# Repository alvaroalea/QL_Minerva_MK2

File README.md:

# SINCLAIR QL - Minerva MK II - New OS + RTC

In 2024 by Alvaro Alea Fernandez

License under: CERN Open Hardware Licence Version 2 - Strongly Reciprocal

https://ohwr.org/cern_ohl_s_v2.txt

My work is only copy the design to Kicad, all (C) are retaing to the original owners.

U1 shall be pin row, to be mounted in the solder side, in a way that allow to insert on the Sinclair QL's Rom socket.

U5 shall be solder without socket under U2.

U2 shall be solder with a socket to allow space for U5.

Original Information of minerva can be found here: http://tfs.firshman.co.uk/ql/minerva.htm

A generic description here: https://wiki.qlforum.co.uk/doku.php?id=qlwiki:minerva

Manuals and software here: https://dilwyn.qlforum.co.uk/docs/manuals/index.html

Main information, GAL code, pictures, etc... has been obtained from this post: https://qlforum.co.uk/viewtopic.php?t=1993

ROM Chip shall be installed as per this picture:

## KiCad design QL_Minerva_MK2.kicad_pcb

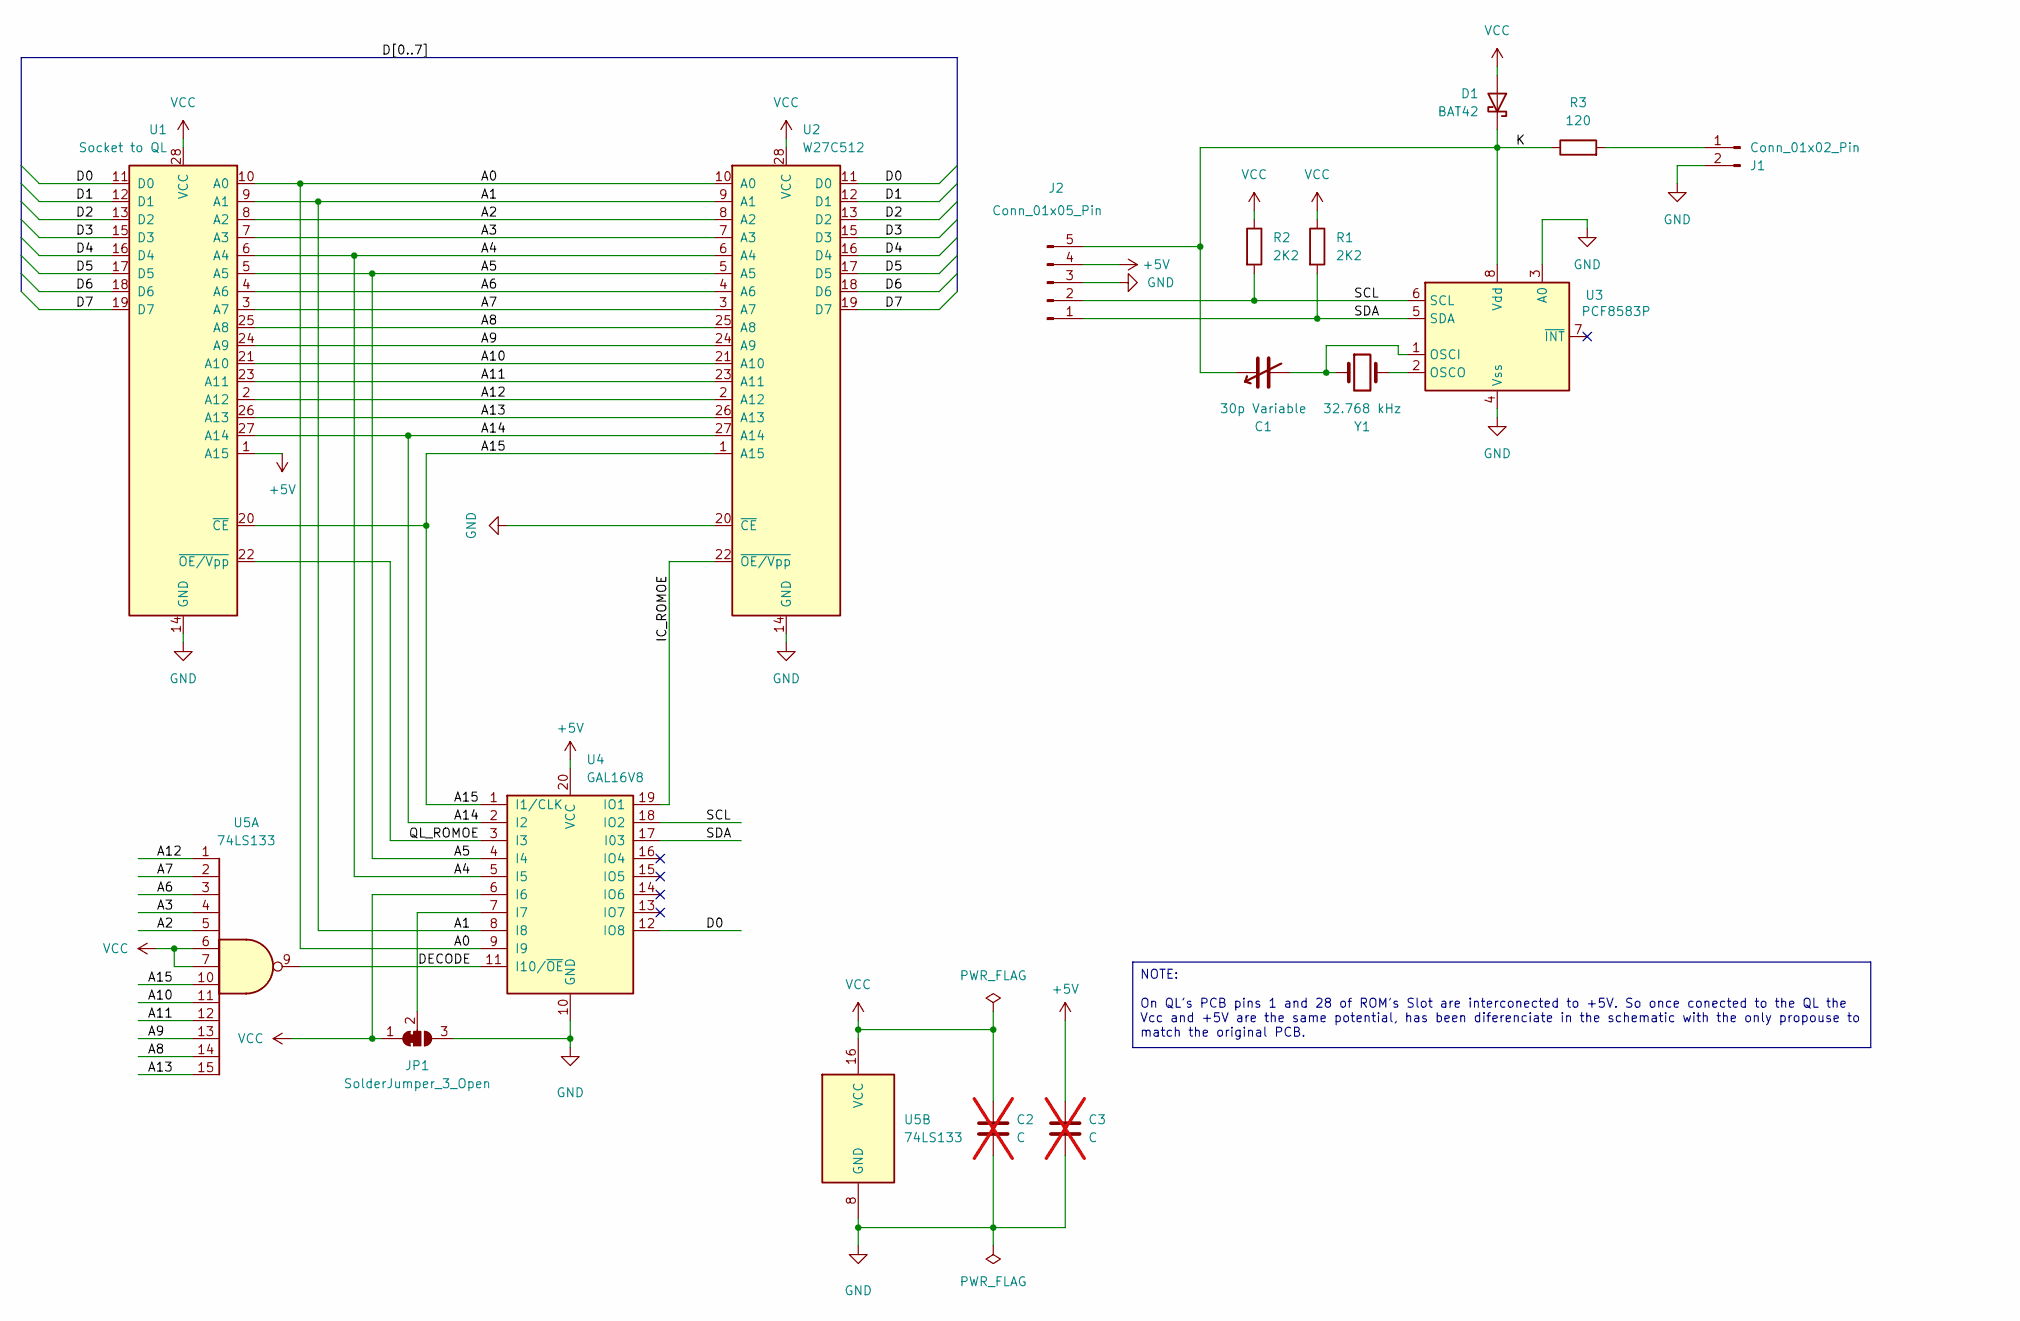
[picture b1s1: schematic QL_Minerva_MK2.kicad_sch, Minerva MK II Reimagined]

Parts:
C1: 30p Variable; C_Variable_Radial_D6.0mm_P5.00mm
C2, C3: C; C_Disc_D3.0mm_W1.6mm_P2.50mm; not fitted
D1: BAT42; D_DO-35_SOD27_P7.62mm_Horizontal
J1: Conn_01x02_Pin; PinHeader_1x02_P2.54mm_Horizontal
J2: Conn_01x05_Pin; PinHeader_1x05_P2.54mm_Horizontal
JP1: SolderJumper_3_Open; SolderJumper-3_P1.3mm_Bridged12_RoundedPad1.0x1.5mm
R1, R2: 2K2; R_Axial_DIN0204_L3.6mm_D1.6mm_P11.17mm_Horizontal
R3: 120; R_Axial_DIN0204_L3.6mm_D1.6mm_P11.17mm_Horizontal
U1: Socket to QL; DIP-28_W15.24mm
U2: W27C512; DIP-28_W15.24mm
U3: PCF8583P; DIP-8_W7.62mm
U4: GAL16V8; DIP-20_W7.62mm
U5: 74LS133; DIP-16_W7.62mm
Y1: 32.768 kHz; Crystal_AT310_D3.0mm_L10.0mm_Horizontal

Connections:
+5V: C3.1, J2.4, U1.1 (A15), U4.20 (VCC)
/A0: U1.10 (A0), U2.10 (A0), U4.9 (I9)
/A1: U1.9 (A1), U2.9 (A1), U4.8 (I8)
/A2: U1.8 (A2), U2.8 (A2), U5.5
/A3: U1.7 (A3), U2.7 (A3), U5.4
/A4: U1.6 (A4), U2.6 (A4), U4.5 (I5)
/A5: U1.5 (A5), U2.5 (A5), U4.4 (I4)
/A6: U1.4 (A6), U2.4 (A6), U5.3
/A7: U1.3 (A7), U2.3 (A7), U5.2
/A8: U1.25 (A8), U2.25 (A8), U5.14
/A9: U1.24 (A9), U2.24 (A9), U5.13
/A10: U1.21 (A10), U2.21 (A10), U5.11
/A11: U1.23 (A11), U2.23 (A11), U5.12
/A12: U1.2 (A12), U2.2 (A12), U5.1
/A13: U1.26 (A13), U2.26 (A13), U5.15
/A14: U1.27 (A14), U2.27 (A14), U4.2 (I2)
/A15: U1.20 (~CE), U2.1 (A15), U4.1 (I1/CLK), U5.10
/D0: U1.11 (D0), U2.11 (D0), U4.12 (IO8)
/D1: U1.12 (D1), U2.12 (D1)
/D2: U1.13 (D2), U2.13 (D2)
/D3: U1.15 (D3), U2.15 (D3)
/D4: U1.16 (D4), U2.16 (D4)
/D5: U1.17 (D5), U2.17 (D5)
/D6: U1.18 (D6), U2.18 (D6)
/D7: U1.19 (D7), U2.19 (D7)
/IC_ROMOE: U2.22 (~OE/Vpp), U4.19 (IO1)
/K: C1.1, D1.1 (K), J2.5, R3.1, U3.8 (Vdd)
/QL_ROMOE: U1.22 (~OE/Vpp), U4.3 (I3)
/SCL: J2.2, R2.2, U3.6 (SCL), U4.18 (IO2)
/SDA: J2.1, R1.2, U3.5 (SDA), U4.17 (I03)
GND: C2.2, C3.2, J1.2, J2.3, JP1.3 (B), U1.14 (GND), U2.14 (GND), U2.20 (~CE), U3.3 (A0), U3.4 (Vss), U4.10 (GND), U5.8 (GND)
unnamed: J1.1, R3.2
unnamed: C1.2, U3.1 (OSCI), Y1.1
unnamed: U3.2 (OSCO), Y1.2
VCC: C2.1, D1.2 (A), JP1.1 (A), R1.1, R2.1, U1.28 (VCC), U2.28 (VCC), U4.6 (I6), U5.6, U5.7, U5.16 (VCC)

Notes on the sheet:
NOTE: On QL's PCB pins 1 and 28 of ROM's Slot are interconected to +5V. So once conected to the QL the Vcc and +5V are the same potential, has been diferenciate in the schematic with the only propouse to match the original PCB.

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
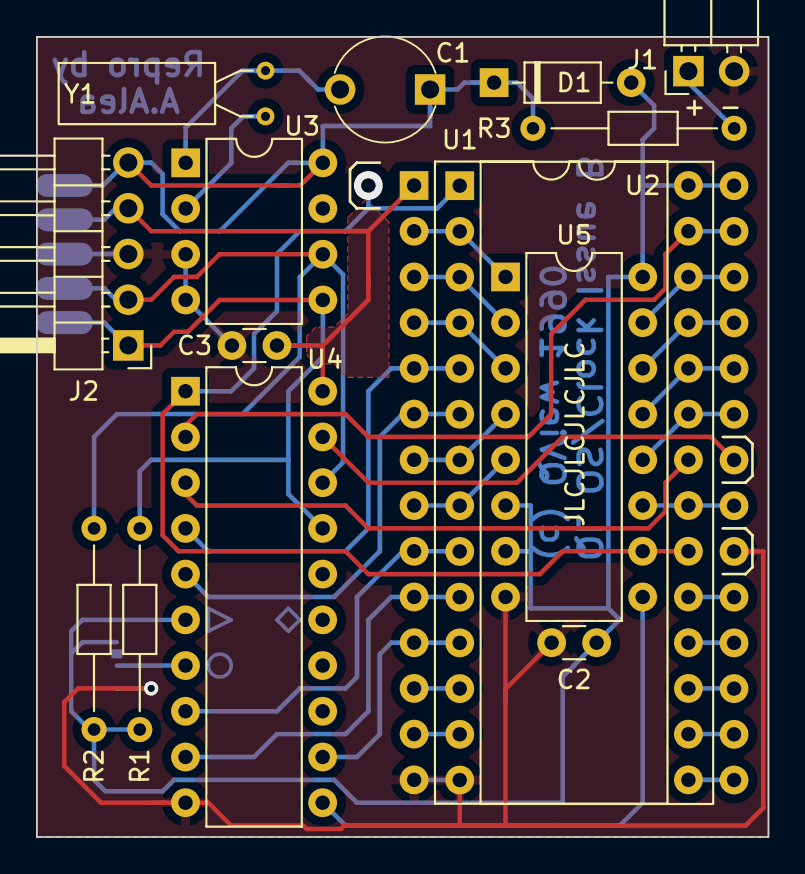
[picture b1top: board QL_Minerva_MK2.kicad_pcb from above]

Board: 2 copper layers, 40.6 x 44.5 mm, 16 parts (1 on the bottom side), 37 nets.

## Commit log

2024-01-27 update pin 6 of GAL
2024-04-28 add values of components
2025-02-23 Fix references
2025-03-25 update C footprint
2025-04-08 fixed error in leg 7 of gal
2025-04-18 Reduced size to avoid colision with cristal of QL Mainboard
2025-05-06 add jedec for select TK2
